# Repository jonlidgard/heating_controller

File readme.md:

# Raspberry Pi Based Heating Controller

The circuit for this is stored under the kicad directory

# Adafruit Python MCP3008

Python code to use the MCP3008 analog to digital converter with a Raspberry Pi or BeagleBone black.

## Installation

To install the library from source (recommended) run the following commands on a Raspberry Pi or other Debian-based OS system:

    sudo apt-get install git build-essential python-dev
    cd ~
    git clone https://github.com/adafruit/Adafruit_Python_MCP3008.git
    cd Adafruit_Python_MCP3008
    sudo python setup.py install

Alternatively you can install from pip with:

    sudo pip install adafruit-mcp3008

Note that the pip install method **won't** install the example code.

#WiringPi

See jonsblog.lidgard.uk/cross-compile
and info held in cpp/build-libDigiPot

# Heating Controller Code

## This code should be run as a daemon

The heating controller connects to a worcester-bosch combi boiler via the TR2 interface (3 4 F) & acts to control demand for heating.
It has it's own TR2 interface for connecting to the existing thermostat but also has 3 'Call For Heat' connections to allow Nest & other devices to control the boiler in a zoned setup.

Control Flow:
* Set the Boiler output to be off using the X9C digital programmable pots.
* Read the TR2 resistances between 3&4 & F&4 to get thermostat mode and sensed temperature.
* Drive the zone valve & when the zone valve is open:
* Set the Boiler output to mimic those resistances using the X9C digital programmable pots.
* If any CFH contacts made, 

Set the X9C to

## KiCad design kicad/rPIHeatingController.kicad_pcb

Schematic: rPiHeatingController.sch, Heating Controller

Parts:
C1, C2, C3, C4, C5, C6, C7, C8, C9, C10, C11, C12, C13, C14: 100n; C_Rect_L4.0mm_W2.5mm_P2.50mm
J1, J2, J15: Screw_Terminal_01x03; TerminalBlock_Altech_AK300-3_P5.00mm
J3, J4, J5, J11, J12, J13, J17, J19: Screw_Terminal_01x02; TerminalBlock_Altech_AK300-2_P5.00mm
J6, J7, J8, J9, J14, J16, J18: Conn_01x06; Pin_Header_Straight_1x06_Pitch2.54mm
J10: Raspberry_Pi_2_3; Socket_Strip_Angled_2x20_Pitch2.54mm
J20: Conn_01x10; Socket_Strip_Straight_1x10_Pitch2.54mm
J21: Conn_01x04_Female; Socket_Strip_Straight_1x04_Pitch2.54mm
J22: Conn_01x03_Female; Socket_Strip_Straight_1x03_Pitch2.54mm
R1, R2, R3, R4, R5, R6: 330R; R_Axial_DIN0207_L6.3mm_D2.5mm_P7.62mm_Horizontal
R7: 4k7; R_Axial_DIN0207_L6.3mm_D2.5mm_P7.62mm_Horizontal
R8: 1k; R_Axial_DIN0207_L6.3mm_D2.5mm_P7.62mm_Horizontal
R9, R11: 3k3; R_Axial_DIN0207_L6.3mm_D2.5mm_P7.62mm_Horizontal
R10: 5k6; R_Axial_DIN0207_L6.3mm_D2.5mm_P7.62mm_Horizontal
R12: 15k; R_Axial_DIN0207_L6.3mm_D2.5mm_P7.62mm_Horizontal
TP1, TP2, TP3: TestPoint; Pin_Header_Angled_1x01_Pitch2.54mm
U1, U2: X9C103P; DIP254P762X533-8
U3: MCP3008; DIP-16_W7.62mm

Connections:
+3V3: J8.3, J9.5, J15.1, J16.5, J20.2, J22.2, R7.1, R8.1, R11.1, R12.1, TP1.1, U3.15 (Vref), U3.16 (Vdd)
+5V: C9.1, C10.1, C11.1, C12.1, C13.1, C14.1, J6.3, J10.2, J10.4, J17.1, J18.1, J20.1, J21.4, J22.1, R1.1, R2.1, R3.1, R4.1, R5.1, R6.1, TP3.1, U1.8, U2.8
ADC1: C1.1, J1.1, R11.2, U3.1 (CH0)
ADC2: C2.1, J1.2, R12.2, U3.2 (CH1)
ADC3: J19.2, R8.2, U3.3 (CH2)
ADC_CLK: J10.12, U3.13 (CLK)
ADC_CS: J10.13, U3.10 (~CS~/SHDN)
ADC_DIN: J10.37, U3.11 (Din)
ADC_DOUT: J10.22, U3.12 (Dout)
CFH1: J9.1, J10.7
CFH2: J9.2, J10.29
CFH3: J9.3, J10.31
CS1_3V: J8.1, J10.35
CS1_5V: J6.1, U1.7
CS2_3V: J8.2, J10.38
CS2_5V: J6.2, U2.7
DS18B20: J10.26, J15.2, R7.2
GND: C1.2, C2.2, C3.2, C4.2, C5.2, C6.2, C7.2, C8.2, C9.2, C10.2, C11.2, C12.2, C13.2, C14.2, J1.3, J3.1, J4.1, J5.1, J6.4, J7.6, J8.4, J9.6, J10.6, J10.9, J10.14, J10.20, J10.25, J10.30, J10.34, J10.39, J11.1, J12.1, J13.1, J14.6, J15.3, J16.6, J17.2, J18.6, J19.1, J20.10, J21.1, J22.3, TP2.1, U1.4, U2.4, U3.9 (DGND), U3.14 (AGND)
INC_3V: J8.5, J10.36
INC_5V: J6.5, U1.1, U2.1
unnamed: C3.1, J3.2, J7.2, R1.2
unnamed: C4.1, J4.2, J7.3, R2.2
unnamed: C5.1, J5.2, J7.4, R3.2
unnamed: C6.1, J11.2, J14.2, R4.2
unnamed: C7.1, J12.2, J14.3, R5.2
unnamed: C8.1, J13.2, J14.4, R6.2
unnamed: J2.1, R9.2, U1.5
unnamed: J2.2, R10.1
unnamed: J2.3, R9.1, U1.6, U2.6
unnamed: J10.8, J21.3
unnamed: J10.10, J21.2
unnamed: J10.19, J20.5
unnamed: J10.21, J20.4
unnamed: J10.23, J20.6
unnamed: J10.24, J20.3
unnamed: J10.27, J20.7
unnamed: J10.28, J20.8
unnamed: J10.40, J20.9
unnamed: R10.2, U2.5
RL1: J10.3, J18.2
RL2: J10.5, J18.3
RL3: J10.32, J18.4
RL4: J10.33, J18.5
UD_3V: J8.6, J10.11
UD_5V: J6.6, U1.2, U2.2
ZV1: J10.15, J16.1
ZV2: J10.16, J16.2
ZV3: J10.18, J16.3

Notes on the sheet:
CFH1
CFH2
CFH3
ZV1
ZV2
ZV3
PWR
RELAYS
TEMP SENSORS
TR2
BOILER
OPTO BOARD
LEVEL SHIFTER
UFH Sensor

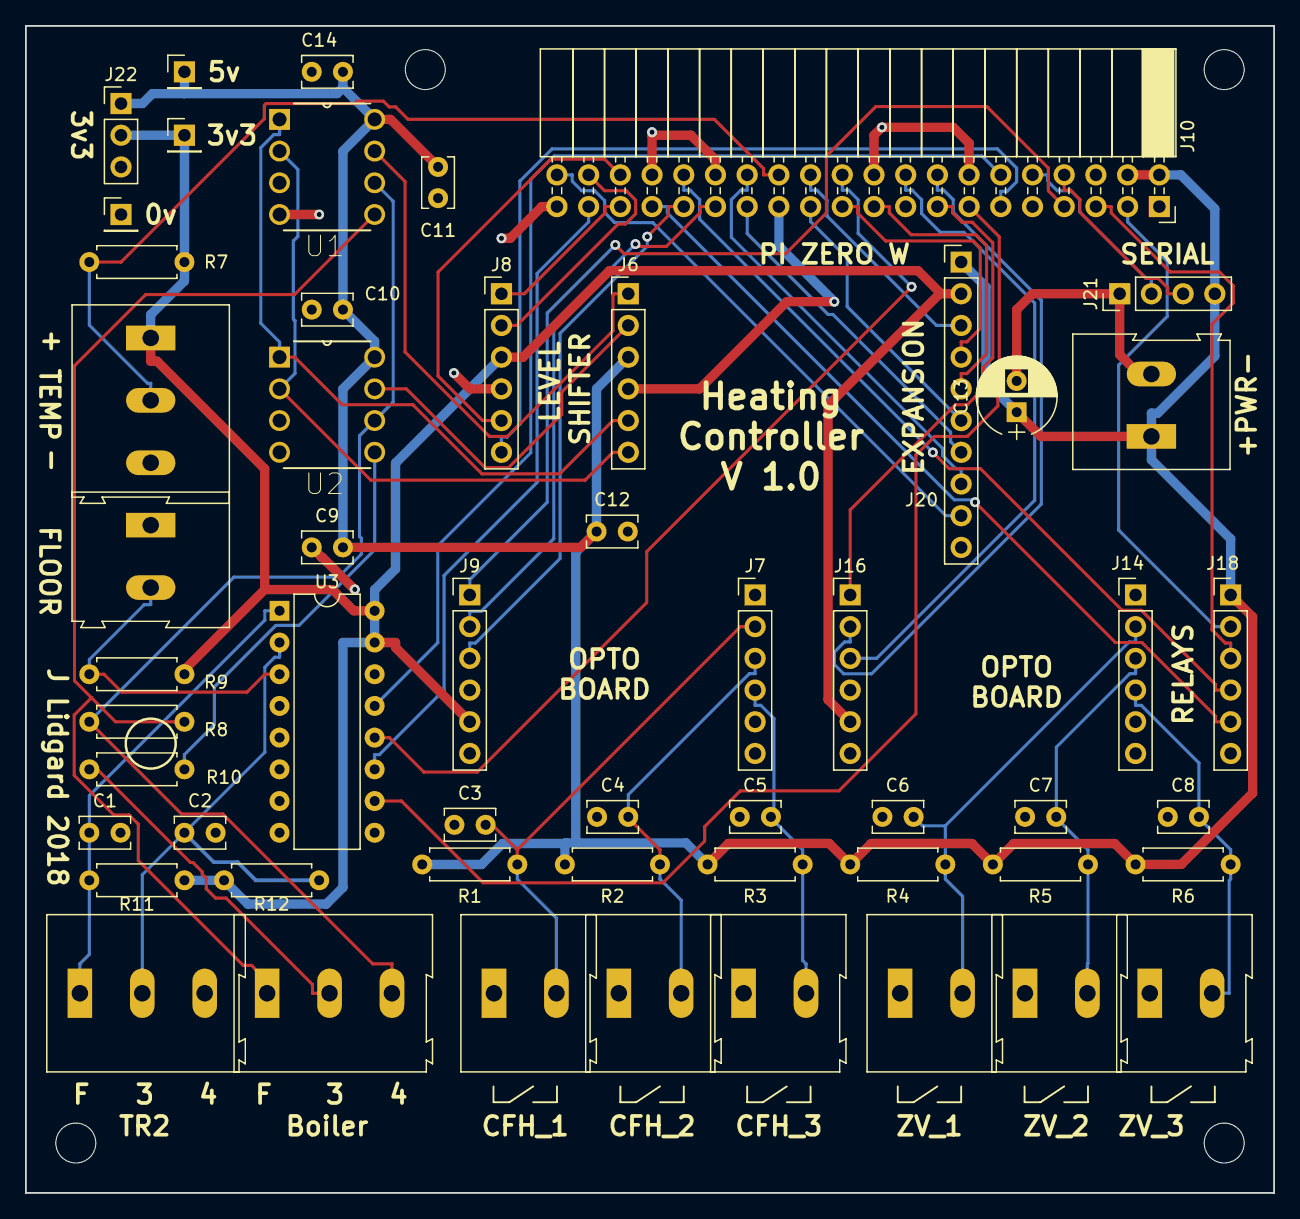
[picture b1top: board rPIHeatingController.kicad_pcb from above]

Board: 2 copper layers, 100.0 x 93.5 mm, 54 parts (0 on the bottom side), 48 nets.

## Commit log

2018-10-09 Early commit
2018-10-09 Moved tests to module __main__
2018-10-09 Fixed a few error but still not working
2018-10-09 Fixed debounce
2018-11-02 more fixes
2018-11-03 A few fixes
2018-11-20 initial working version
2018-11-20 logging changes
2019-11-02 Updated to use Nextion display
2019-11-02 Added Colour
2019-11-02 Fixed missing Boiler widget
2019-11-02 Added filesystem status file - heatingStatus
